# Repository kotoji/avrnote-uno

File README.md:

# Avrnote UNO R3

Arduino UNO R3 互換の自作基盤です。KiCAD の練習目的で作成しました。

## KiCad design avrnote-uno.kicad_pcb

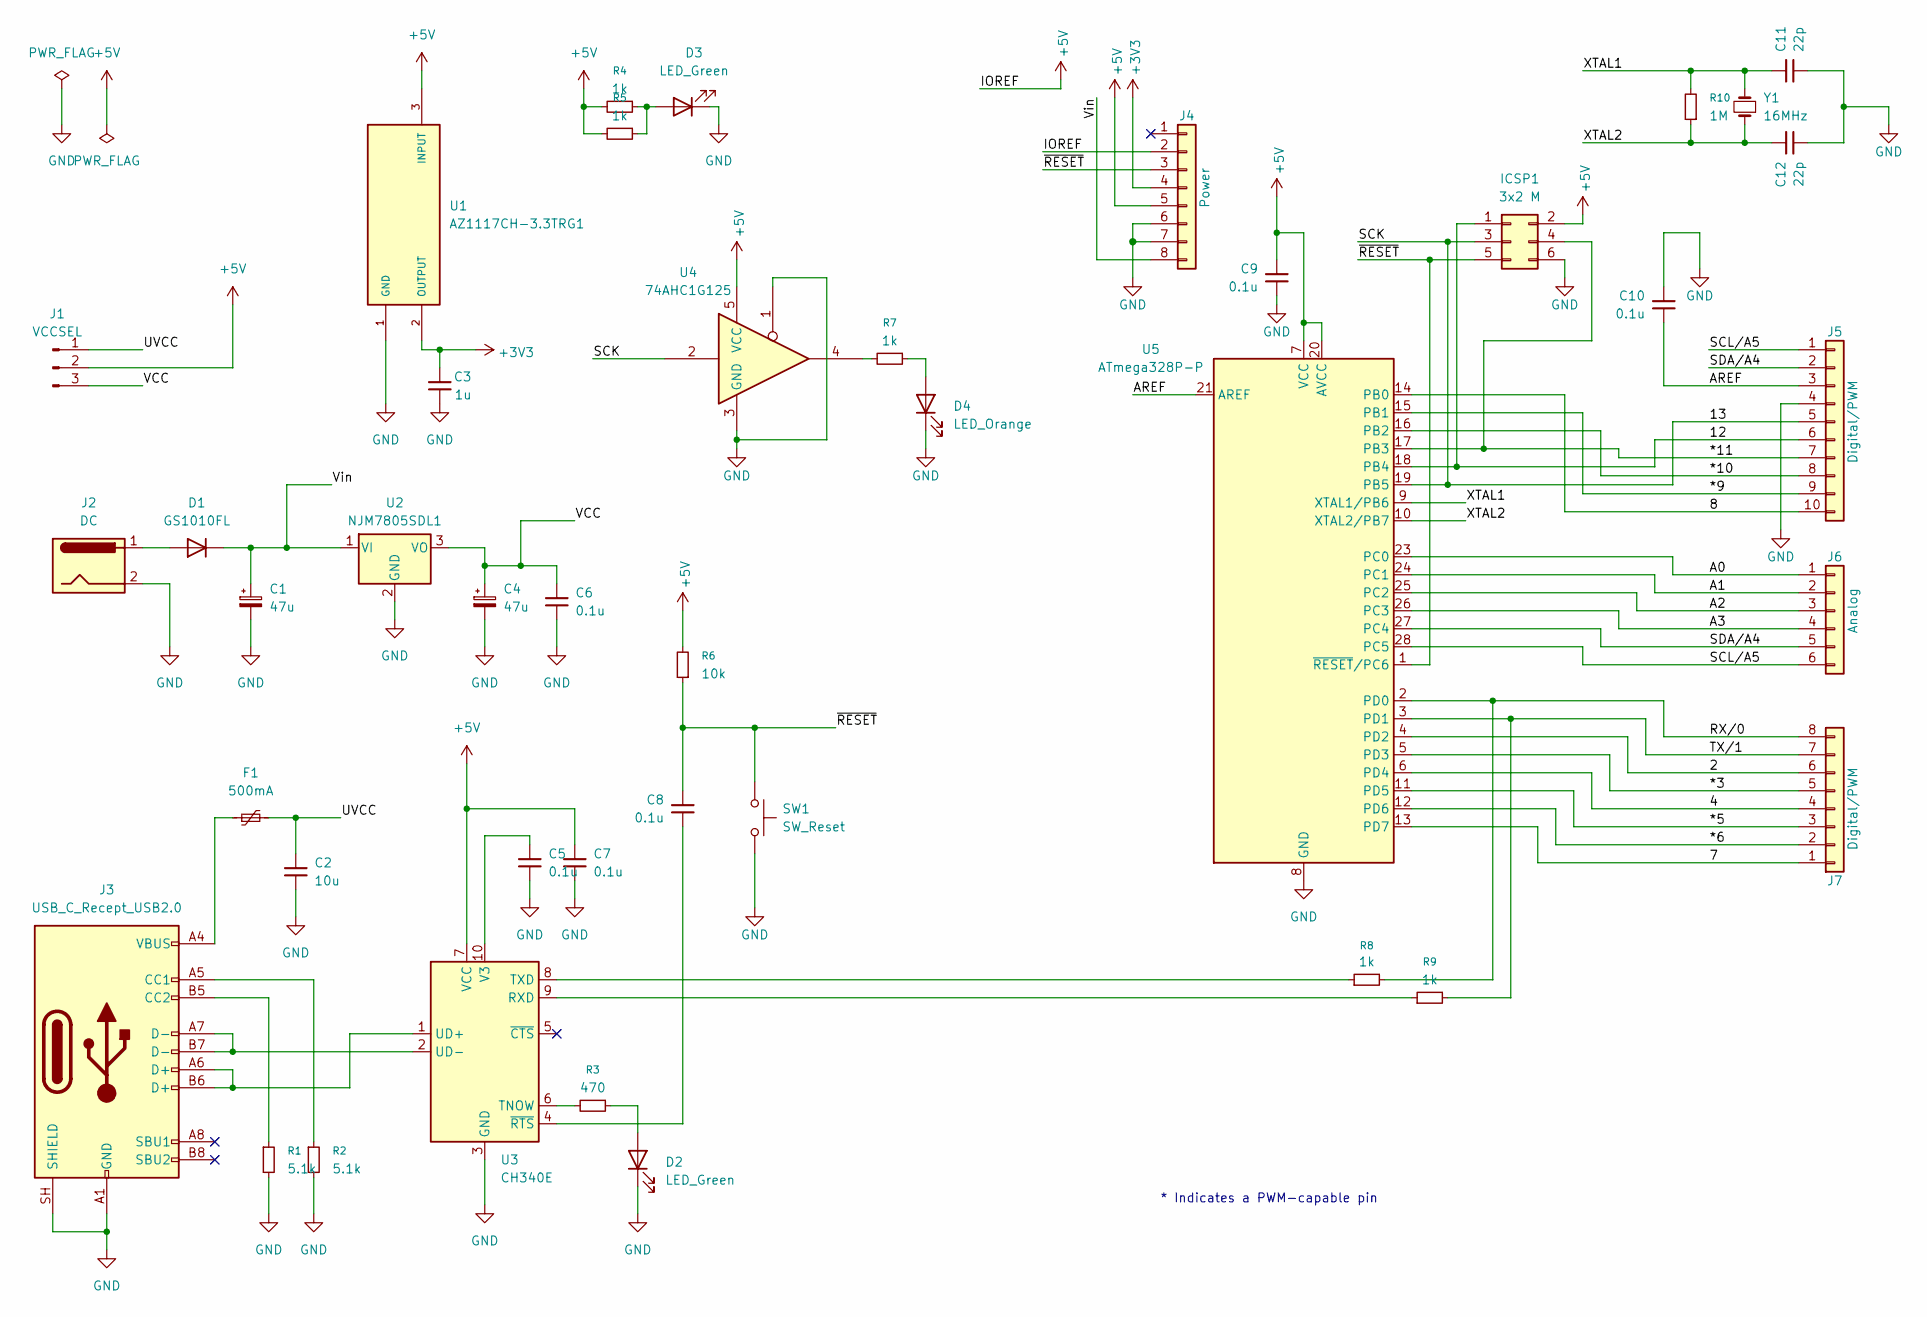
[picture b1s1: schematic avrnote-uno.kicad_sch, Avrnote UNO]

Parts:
C1, C4: 47u; CP_Elec_6.3x5.4
C2: 10u; C_1206_3216Metric
C3: 1u; C_0603_1608Metric
C5, C6, C7, C8, C9, C10: 0.1u; C_0603_1608Metric
C11, C12: 22p; C_0603_1608Metric
D1: GS1010FL; Nexperia_CFP3_SOD-123W
D2, D3: LED_Green; LED_0603_1608Metric
D4: LED_Orange; LED_0603_1608Metric
F1: 500mA; Fuse_1206_3216Metric
ICSP1: 3x2 M; PinHeader_2x03_P2.54mm_Vertical
J1: VCCSEL; PinHeader_1x03_P2.54mm_Vertical
J2: DC; BarrelJack_Horizontal
J3: USB_C_Recept_USB2.0; USB_C_Receptacle_G-Switch_GT-USB-7010ASV
J4: Power; PinSocket_1x08_P2.54mm_Vertical
J5: Digital/PWM; PinSocket_1x10_P2.54mm_Vertical
J6: Analog; PinSocket_1x06_P2.54mm_Vertical
J7: Digital/PWM; PinSocket_1x08_P2.54mm_Vertical
R1, R2: 5.1k; R_0603_1608Metric
R3: 470; R_0603_1608Metric
R4, R5, R7, R8, R9: 1k; R_0603_1608Metric
R6: 10k; R_0603_1608Metric
R10: 1M; R_0603_1608Metric
SW1: SW_Reset; SW_PUSH_6mm
U1: AZ1117CH-3.3TRG1; VREG_AZ1117CH-3.3TRG1; PARTREV 5 - 2
U2: NJM7805SDL1; ATPAK-2
U3: CH340E; MSOP-10_3x3mm_P0.5mm
U4: 74AHC1G125; SOT-23-5
U5: ATmega328P-P; DIP-28_W7.62mm
Y1: 16MHz; XTAL_HC49P488W43L1085T450H368

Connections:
+3V3: C3.1, J4.4, U1.2 (OUTPUT), U1.4 (OUTPUT)
+5V: C7.1, C9.1, ICSP1.2, J1.2, J4.2, J4.5, R4.2, R5.2, R6.2, U1.3 (INPUT), U3.7 (VCC), U4.5 (VCC), U5.7 (VCC), U5.20 (AVCC); also elsewhere on the board
/2: J7.6, U5.4 (PD2)
/4: J7.4, U5.6 (PD4)
/7: J7.1, U5.13 (PD7)
/8: J5.10, U5.14 (PB0)
/12: ICSP1.1, J5.6, U5.18 (PB4); also elsewhere on the board
/13: ICSP1.3, J5.5, U4.2, U5.19 (PB5); also elsewhere on the board
/*3: J7.5, U5.5 (PD3)
/*5: J7.3, U5.11 (PD5)
/*6: J7.2, U5.12 (PD6)
/*9: J5.9, U5.15 (PB1)
/*10: J5.8, U5.16 (PB2)
/*11: ICSP1.4, J5.7, U5.17 (PB3); also elsewhere on the board
/A0: J6.1, U5.23 (PC0)
/A1: J6.2, U5.24 (PC1)
/A2: J6.3, U5.25 (PC2)
/A3: J6.4, U5.26 (PC3)
/AREF: C10.2, J5.3, U5.21 (AREF)
/RX/0: J7.8, R8.2, U5.2 (PD0)
/SCL/A5: J5.1, J6.6, U5.28 (PC5)
/SDA/A4: J5.2, J6.5, U5.27 (PC4)
/TX/1: J7.7, R9.2, U5.3 (PD1)
/UVCC: C2.1, F1.2, J1.1
/VCC: C4.1, C6.1, J1.3, U2.3 (VO)
/Vin: C1.1, D1.1 (K), J4.8, U2.1 (VI)
/XTAL1: C11.1, R10.2, U5.9 (XTAL1/PB6), Y1.2
/XTAL2: C12.1, R10.1, U5.10 (XTAL2/PB7), Y1.1
/~RESET: C8.1, ICSP1.5, J4.3, R6.1, SW1.1, U5.1 (~RESET/PC6); also elsewhere on the board
GND: C1.2, C2.2, C3.2, C4.2, C5.2, C6.2, C7.2, C9.2, C10.1, C11.2, C12.2, D2.1 (K), D3.1 (K), D4.1 (K), ICSP1.6, J2.2, J3.A1 (GND), J3.A12 (GND), J3.B1 (GND), J3.B12 (GND), J3.SH (SHIELD), J4.6, J4.7, J5.4, R1.2, R2.2, SW1.2, U1.1 (GND), U2.2 (GND), U3.3 (GND), U4.1, U4.3 (GND), U5.8 (GND), U5.22 (GND); also elsewhere on the board
unnamed: D1.2 (A), J2.1
unnamed: D2.2 (A), R3.1
unnamed: D3.2 (A), R4.1, R5.1
unnamed: D4.2 (A), R7.1
unnamed: F1.1, J3.A4 (VBUS), J3.A9 (VBUS), J3.B4 (VBUS), J3.B9 (VBUS)
unnamed: J3.A5 (CC1), R2.1
unnamed: J3.B5 (CC2), R1.1
unnamed: R7.2, U4.4
unnamed: R9.1, U3.9 (RXD)
unnamed: R3.2, U3.6 (TNOW)
unnamed: R8.1, U3.8 (TXD)
unnamed: J3.A6 (D+), J3.B6 (D+), U3.1 (UD+)
unnamed: J3.A7 (D-), J3.B7 (D-), U3.2 (UD-)
unnamed: C5.1, U3.10 (V3)
unnamed: C8.2, U3.4 (~RTS)

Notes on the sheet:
* Indicates a PWM-capable pin

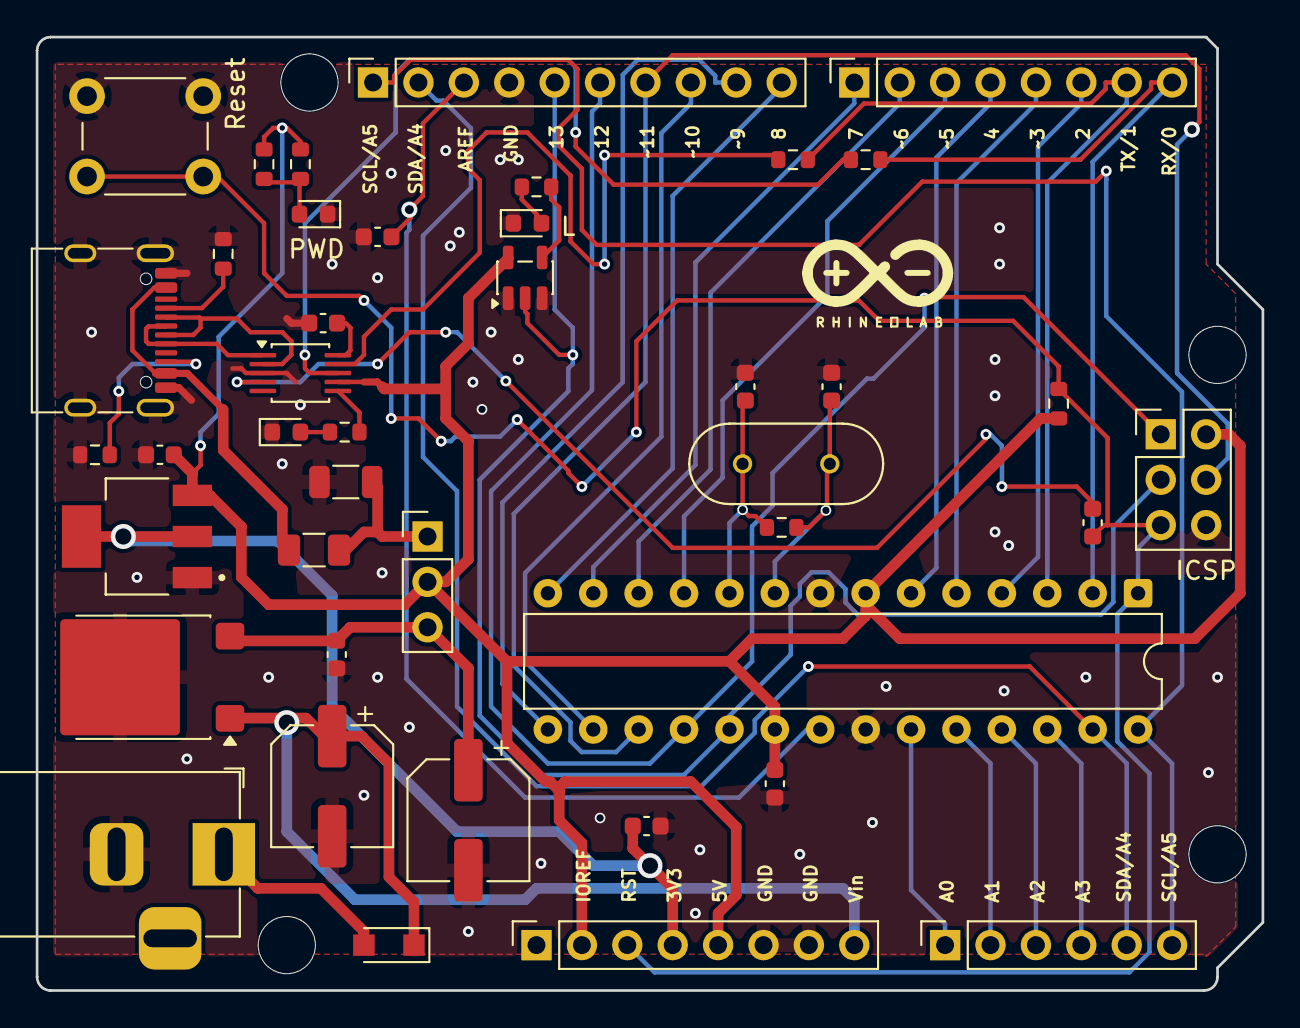
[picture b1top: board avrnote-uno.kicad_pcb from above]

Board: 2 copper layers, 68.6 x 53.3 mm, 46 parts (0 on the bottom side), 45 nets.

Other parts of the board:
ICSP: 3x2 M; PinHeader_2x03_P2.54mm_Vertical
MH1, MH2, MH3, MH4: MountingHole_3.2mm

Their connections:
+5V: ICSP.2; also elsewhere on the board
/12: ICSP.1; also elsewhere on the board
/13: ICSP.3; also elsewhere on the board
/*11: ICSP.4; also elsewhere on the board
/~RESET: ICSP.5; also elsewhere on the board
GND: ICSP.6; also elsewhere on the board
